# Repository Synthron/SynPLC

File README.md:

# SynPLC

Open Source modular PLC with Microcontrollers

**WORK IN PROGRESS**

# To-Dos

## Repo

- [x] Rewrite documentation in english
- [x] add reviewed PCBs
- [ ] fill out tech specs of modules once programmed
- [ ] Cleanup Repo
  - [ ] better folder structure
  - [X] delete obsolete files

## Hardware

- [x] Order new PCBs with STM32s
- [x] Assemble new PCBs
- [ ] Test new hardware
  - [X] DO
  - [X] DI
  - [ ] AO
  - [ ] AI
  - [ ] XT
- [ ] New Modules
  - [ ] CPU V2
    - [X] Layout
    - [X] Review
    - [ ] Ordered
  - [ ] Relais Module
  - [ ] PWM Module

## Software

- [ ] Write Software for new PCBs
  - [ ] CPU
  - [ ] DO
  - [ ] DI
  - [ ] AO
  - [ ] AI
  - [ ] XT
- [ ] Porting of SR485 protocol to new hardware
  - [ ] Make it use Interrupts
  - [ ] Make it more efficient (processing)
  - [ ] implement failsafes when no answer
- [ ] Define and program CAN protocol
- [ ] Write generalized Code for CPU
- [ ] ~~define structured Text~~ (postponed)
- [ ] ~~import structured text and parse into running code~~ (postponed)

## Possible Fixes

- [x] ~~MAX485 with 5V supply voltage on all IO modules ?~~
  - changed to 3V3 on the CPU
- [x] DIs and DO (alt. switches) re-soldering (dead channels)
- [x] better connector for CPU
- [ ] parametrize RS485 lib a bit more (tbd)

## issues

- [x] weird additional bytes sent by slave after ACK and CS???
  - resolved

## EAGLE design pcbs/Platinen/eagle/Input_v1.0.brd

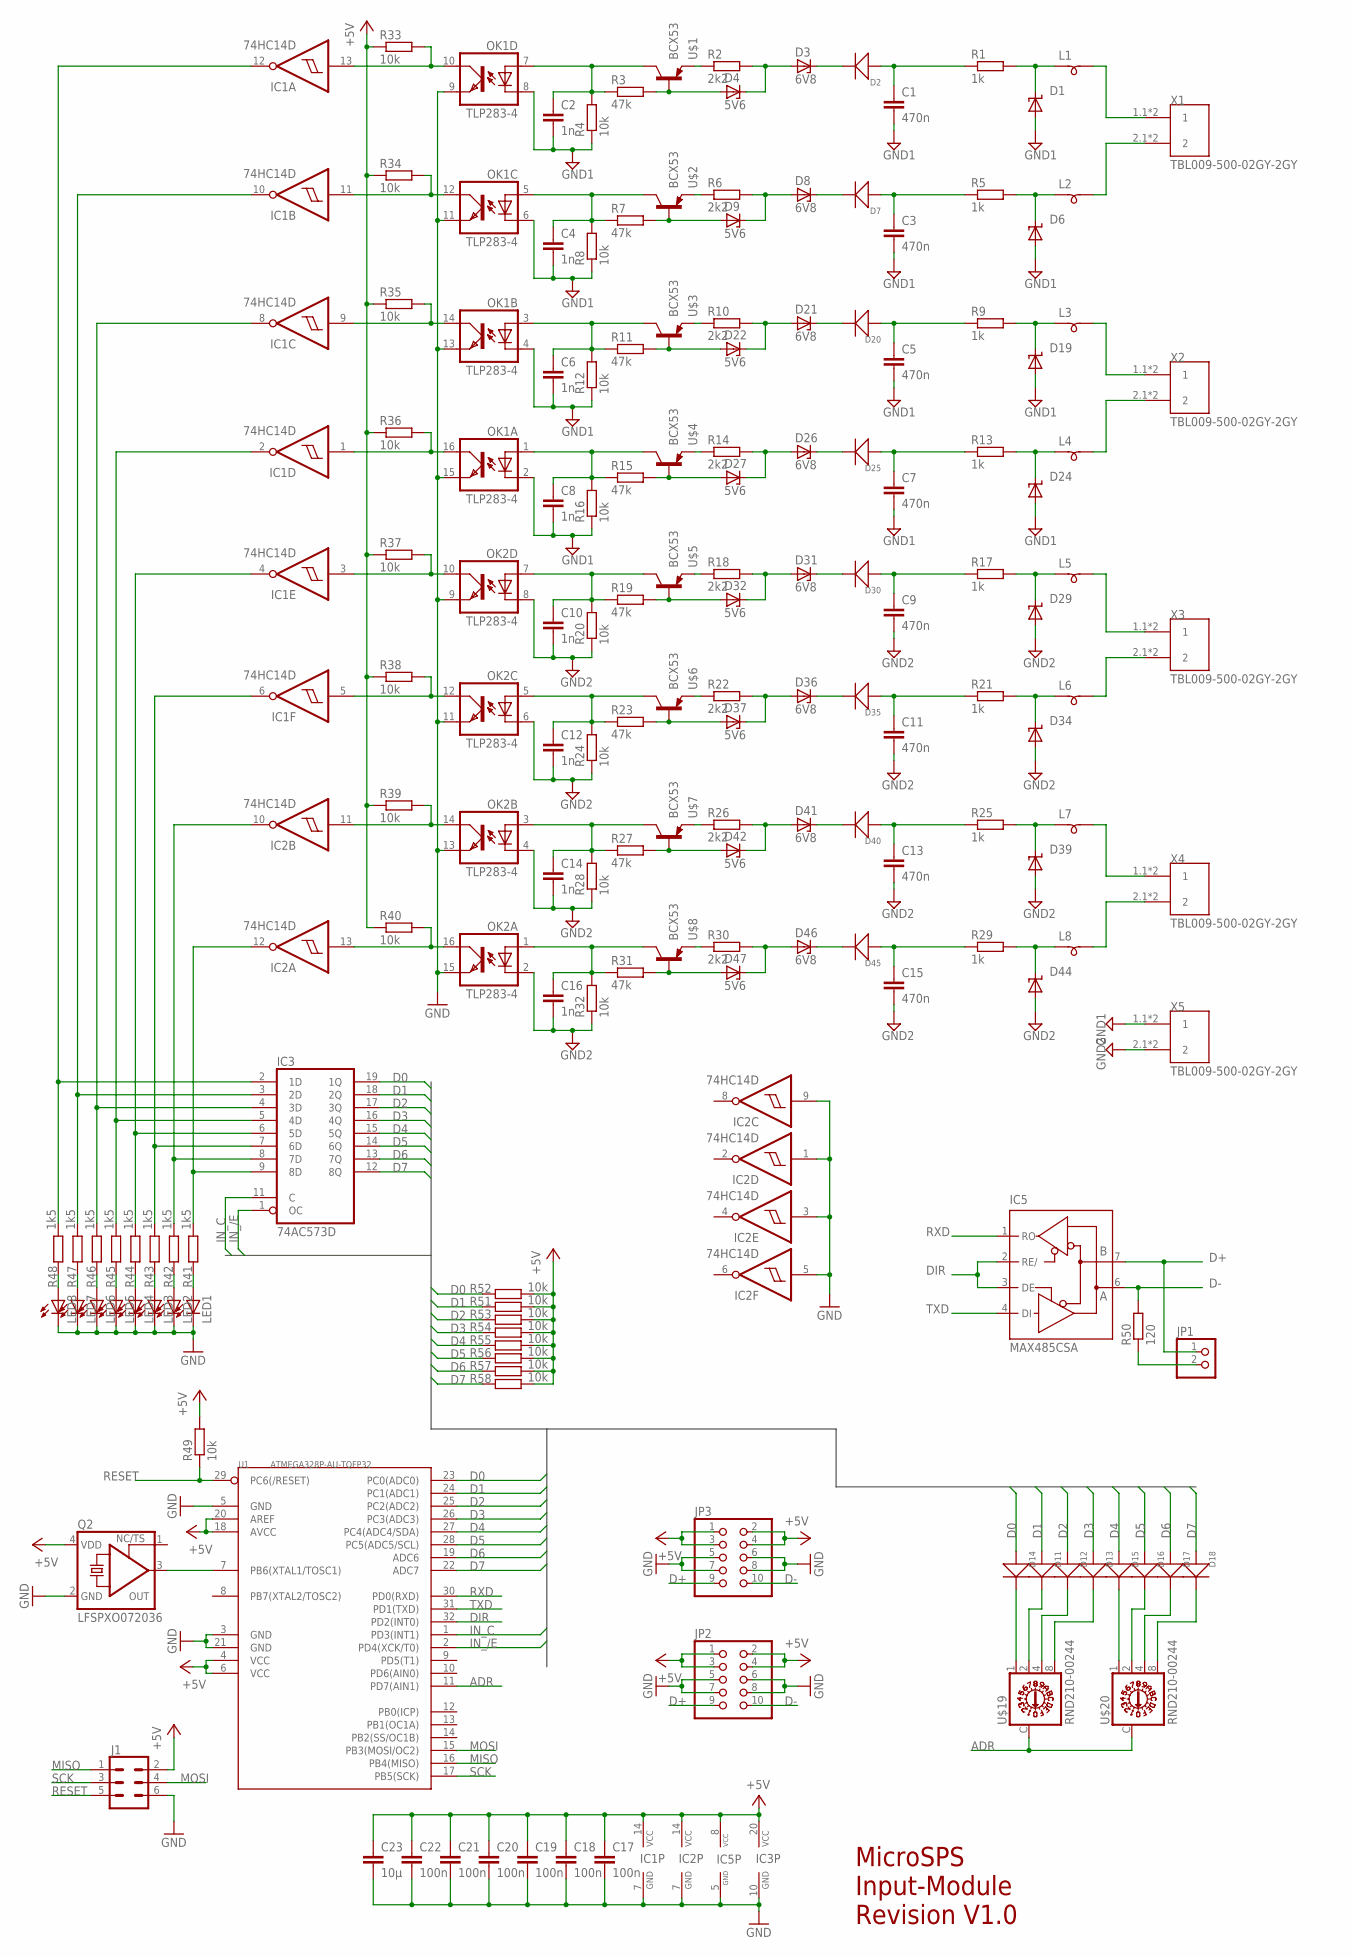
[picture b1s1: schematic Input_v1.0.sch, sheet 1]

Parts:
C1, C3, C5, C7, C9, C11, C13, C15: 470n; C0805
C2, C4, C6, C8, C10, C12, C14, C16: 1n; C0805
C17, C18, C19, C20, C21, C22: 100n; C0805
C23: 10µ; C0805
D1, D6, D19, D24, D29, D34, D39, D44: SUPPRESSOR-SMBJ; SMBJ
D2, D7, D11, D12, D13, D14, D15, D16, D17, D18, D20, D25, D30, D35, D40, D45: DIODE'1N4148-SMD'; LL-34
D3, D8, D21, D26, D31, D36, D41, D46: 6V8; SOD80C
D4, D9, D22, D27, D32, D37, D42, D47: 5V6; SOD80C
IC1, IC2: 74HC14D; SO14
IC3: 74AC573D; SO20W
IC5: MAX485CSA; SO08
J1: CONN_03X2FEMALE_SMD; 2X3_SMD
JP1: PINHD-1X2; 1X02
JP2, JP3: PINHD-2X5/90; 2X05/90
L1, L2, L3, L4, L5, L6, L7, L8: SM-B5
LED1, LED2, LED3, LED4, LED5, LED6, LED7, LED8: LED3MM
OK1, OK2: TLP283-4; MINI-FLAT-16
Q2: LFSPXO072036; 5.0X3.2_KXO-56
R1, R5, R9, R13, R17, R21, R25, R29: 1k; R0805
R2, R6, R10, R14, R18, R22, R26, R30: 2k2; R0805
R3, R7, R11, R15, R19, R23, R27, R31: 47k; R0805
R4, R8, R12, R16, R20, R24, R28, R32, R33, R34, R35, R36, R37, R38, R39, R40, R49, R51, R52, R53, R54, R55, R56, R57, R58: 10k; R0805
R41, R42, R43, R44, R45, R46, R47, R48: 1k5; R0805
R50: 120; R0805
U1: ATMEGA328P-AU-TQFP32; TQFP32-0.8-7X7MM
U$1, U$2, U$3, U$4, U$5, U$6, U$7, U$8: BCX53; SOT89
U$19, U$20: RND210-00244
X1, X2, X3, X4, X5: TBL009-500-02GY-2GY

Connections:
+5V: C17.1, C18.1, C19.1, C20.1, C21.1, C22.1, C23.1, IC1.14 (VCC), IC2.14 (VCC), IC3.20 (VCC), IC5.8 (VCC), J1.2, JP2.1, JP2.2, JP2.3, JP2.4, JP3.1, JP3.2, JP3.3, JP3.4, Q2.4 (VDD), R33.1, R34.1, R35.1, R36.1, R37.1, R38.1, R39.1, R40.1, R49.2, R51.2, R52.2, R53.2, R54.2, R55.2, R56.2, R57.2, R58.2, U1.4 (VCC), U1.6 (VCC), U1.18 (AVCC), U1.20 (AREF)
ADR: U1.11 (PD7(AIN1)), U$19.C, U$20.C
D0: D14.A (+), IC3.19 (1Q), R52.1, U1.23 (PC0(ADC0))
D1: D11.A (+), IC3.18 (2Q), R51.1, U1.24 (PC1(ADC1))
D2: D12.A (+), IC3.17 (3Q), R53.1, U1.25 (PC2(ADC2))
D3: D13.A (+), IC3.16 (4Q), R54.1, U1.26 (PC3(ADC3))
D4: D15.A (+), IC3.15 (5Q), R55.1, U1.27 (PC4(ADC4/SDA))
D5: D16.A (+), IC3.14 (6Q), R56.1, U1.28 (PC5(ADC5/SCL))
D6: D17.A (+), IC3.13 (7Q), R57.1, U1.19 (ADC6)
D7: D18.A (+), IC3.12 (8Q), R58.1, U1.22 (ADC7)
D+: IC5.7 (B), JP1.1, JP2.9, JP3.9
D-: IC5.6 (A), JP2.10, JP3.10, R50.2
DIR: IC5.2 (RE/), IC5.3 (DE), U1.32 (PD2(INT0))
GND: C17.2, C18.2, C19.2, C20.2, C21.2, C22.2, C23.2, IC1.7 (GND), IC2.1 (I), IC2.3 (I), IC2.5 (I), IC2.7 (GND), IC2.9 (I), IC3.10 (GND), IC5.5 (GND), J1.6, JP2.5, JP2.6, JP2.7, JP2.8, JP3.5, JP3.6, JP3.7, JP3.8, LED1.K (C), LED2.K (C), LED3.K (C), LED4.K (C), LED5.K (C), LED6.K (C), LED7.K (C), LED8.K (C), OK1.9 (EMIT), OK1.11 (EMIT), OK1.13 (EMIT), OK1.15 (EMIT), OK2.9 (EMIT), OK2.11 (EMIT), OK2.13 (EMIT), OK2.15 (EMIT), Q2.2 (GND), U1.3 (GND), U1.5 (GND), U1.21 (GND)
GND1: C1.2, C2.2, C3.2, C4.2, C5.2, C6.2, C7.2, C8.2, D1.A, D6.A, D19.A, D24.A, OK1.2 (C), OK1.4 (C), OK1.6 (C), OK1.8 (C), R4.1, R8.1, R12.1, R16.1, X5.1.1 (1), X5.1.2 (1)
GND2: C9.2, C10.2, C11.2, C12.2, C13.2, C14.2, C15.2, C16.2, D29.A, D34.A, D39.A, D44.A, OK2.2 (C), OK2.4 (C), OK2.6 (C), OK2.8 (C), R20.1, R24.1, R28.1, R32.1, X5.2.1 (2), X5.2.2 (2)
IN_/E: IC3.1 (OC), U1.2 (PD4(XCK/T0))
IN_C: IC3.11 (C), U1.1 (PD3(INT1))
MISO: J1.1, U1.16 (PB4(MISO))
MOSI: J1.4, U1.15 (PB3(MOSI/OC2))
unnamed: D3.A, D4.C, R2.2
unnamed: D2.C (-), D3.C
unnamed: C1.1, D2.A (+), R1.1
unnamed: D1.C, L1.1, R1.2
unnamed: D4.A, R3.2, U$1.1 (B)
unnamed: R2.1, U$1.3 (E)
unnamed: C2.1, OK1.7 (A), R3.1, R4.2, U$1.2 (C), U$1.2.1 (C)
unnamed: IC1.13 (I), OK1.10 (COL), R33.2
unnamed: L1.2, X1.1.1 (1), X1.1.2 (1)
unnamed: D8.A, D9.C, R6.2
unnamed: D7.C (-), D8.C
unnamed: C3.1, D7.A (+), R5.1
unnamed: D6.C, L2.1, R5.2
unnamed: R6.1, U$2.3 (E)
unnamed: L2.2, X1.2.1 (2), X1.2.2 (2)
unnamed: D9.A, R7.2, U$2.1 (B)
unnamed: C4.1, OK1.5 (A), R7.1, R8.2, U$2.2 (C), U$2.2.1 (C)
unnamed: IC1.11 (I), OK1.12 (COL), R34.2
unnamed: D21.A, D22.C, R10.2
unnamed: D20.C (-), D21.C
unnamed: C5.1, D20.A (+), R9.1
unnamed: D19.C, L3.1, R9.2
unnamed: R10.1, U$3.3 (E)
unnamed: L3.2, X2.1.1 (1), X2.1.2 (1)
unnamed: D22.A, R11.2, U$3.1 (B)
unnamed: C6.1, OK1.3 (A), R11.1, R12.2, U$3.2 (C), U$3.2.1 (C)
unnamed: IC1.9 (I), OK1.14 (COL), R35.2
unnamed: D26.A, D27.C, R14.2
unnamed: D25.C (-), D26.C
unnamed: C7.1, D25.A (+), R13.1
unnamed: D24.C, L4.1, R13.2
unnamed: R14.1, U$4.3 (E)
unnamed: L4.2, X2.2.1 (2), X2.2.2 (2)
unnamed: D27.A, R15.2, U$4.1 (B)
unnamed: C8.1, OK1.1 (A), R15.1, R16.2, U$4.2 (C), U$4.2.1 (C)
unnamed: IC1.1 (I), OK1.16 (COL), R36.2
unnamed: D31.A, D32.C, R18.2
unnamed: D30.C (-), D31.C
unnamed: C9.1, D30.A (+), R17.1
unnamed: D29.C, L5.1, R17.2
unnamed: R18.1, U$5.3 (E)
unnamed: L5.2, X3.1.1 (1), X3.1.2 (1)
unnamed: D32.A, R19.2, U$5.1 (B)
unnamed: C10.1, OK2.7 (A), R19.1, R20.2, U$5.2 (C), U$5.2.1 (C)
unnamed: IC1.3 (I), OK2.10 (COL), R37.2
unnamed: D36.A, D37.C, R22.2
unnamed: D35.C (-), D36.C
unnamed: C11.1, D35.A (+), R21.1
unnamed: D34.C, L6.1, R21.2
unnamed: R22.1, U$6.3 (E)
unnamed: L6.2, X3.2.1 (2), X3.2.2 (2)
unnamed: D37.A, R23.2, U$6.1 (B)
unnamed: C12.1, OK2.5 (A), R23.1, R24.2, U$6.2 (C), U$6.2.1 (C)
unnamed: IC1.5 (I), OK2.12 (COL), R38.2
unnamed: D41.A, D42.C, R26.2
unnamed: D40.C (-), D41.C
unnamed: C13.1, D40.A (+), R25.1
unnamed: D39.C, L7.1, R25.2
unnamed: R26.1, U$7.3 (E)
unnamed: L7.2, X4.1.1 (1), X4.1.2 (1)
unnamed: D42.A, R27.2, U$7.1 (B)
unnamed: C14.1, OK2.3 (A), R27.1, R28.2, U$7.2 (C), U$7.2.1 (C)
unnamed: IC2.11 (I), OK2.14 (COL), R39.2
unnamed: D46.A, D47.C, R30.2
unnamed: D45.C (-), D46.C
unnamed: C15.1, D45.A (+), R29.1
unnamed: D44.C, L8.1, R29.2
unnamed: R30.1, U$8.3 (E)
unnamed: L8.2, X4.2.1 (2), X4.2.2 (2)
unnamed: D47.A, R31.2, U$8.1 (B)
unnamed: C16.1, OK2.1 (A), R31.1, R32.2, U$8.2 (C), U$8.2.1 (C)
unnamed: IC2.13 (I), OK2.16 (COL), R40.2
unnamed: IC1.12 (O), IC3.2 (1D), R48.2
unnamed: IC1.10 (O), IC3.3 (2D), R47.2
unnamed: IC1.8 (O), IC3.4 (3D), R46.2
unnamed: IC1.2 (O), IC3.5 (4D), R45.2
unnamed: IC1.4 (O), IC3.6 (5D), R44.2
unnamed: IC1.6 (O), IC3.7 (6D), R43.2
unnamed: IC2.10 (O), IC3.8 (7D), R42.2
unnamed: IC2.12 (O), IC3.9 (8D), R41.2
unnamed: LED8.A, R48.1
unnamed: LED7.A, R47.1
unnamed: LED6.A, R46.1
unnamed: LED5.A, R45.1
unnamed: LED4.A, R44.1
unnamed: LED3.A, R43.1
unnamed: LED2.A, R42.1
unnamed: LED1.A, R41.1
unnamed: Q2.3 (OUT), U1.7 (PB6(XTAL1/TOSC1))
unnamed: JP1.2, R50.1
unnamed: D14.C (-), U$19.1
unnamed: D11.C (-), U$19.2
unnamed: D12.C (-), U$19.4
unnamed: D13.C (-), U$19.8
unnamed: D15.C (-), U$20.1
unnamed: D16.C (-), U$20.2
unnamed: D17.C (-), U$20.4
unnamed: D18.C (-), U$20.8
RESET: J1.5, R49.1, U1.29 (PC6(/RESET))
RXD: IC5.1 (RO), U1.30 (PD0(RXD))
SCK: J1.3, U1.17 (PB5(SCK))
TXD: IC5.4 (DI), U1.31 (PD1(TXD))

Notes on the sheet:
MicroSPS Input-Module Revision V1.0

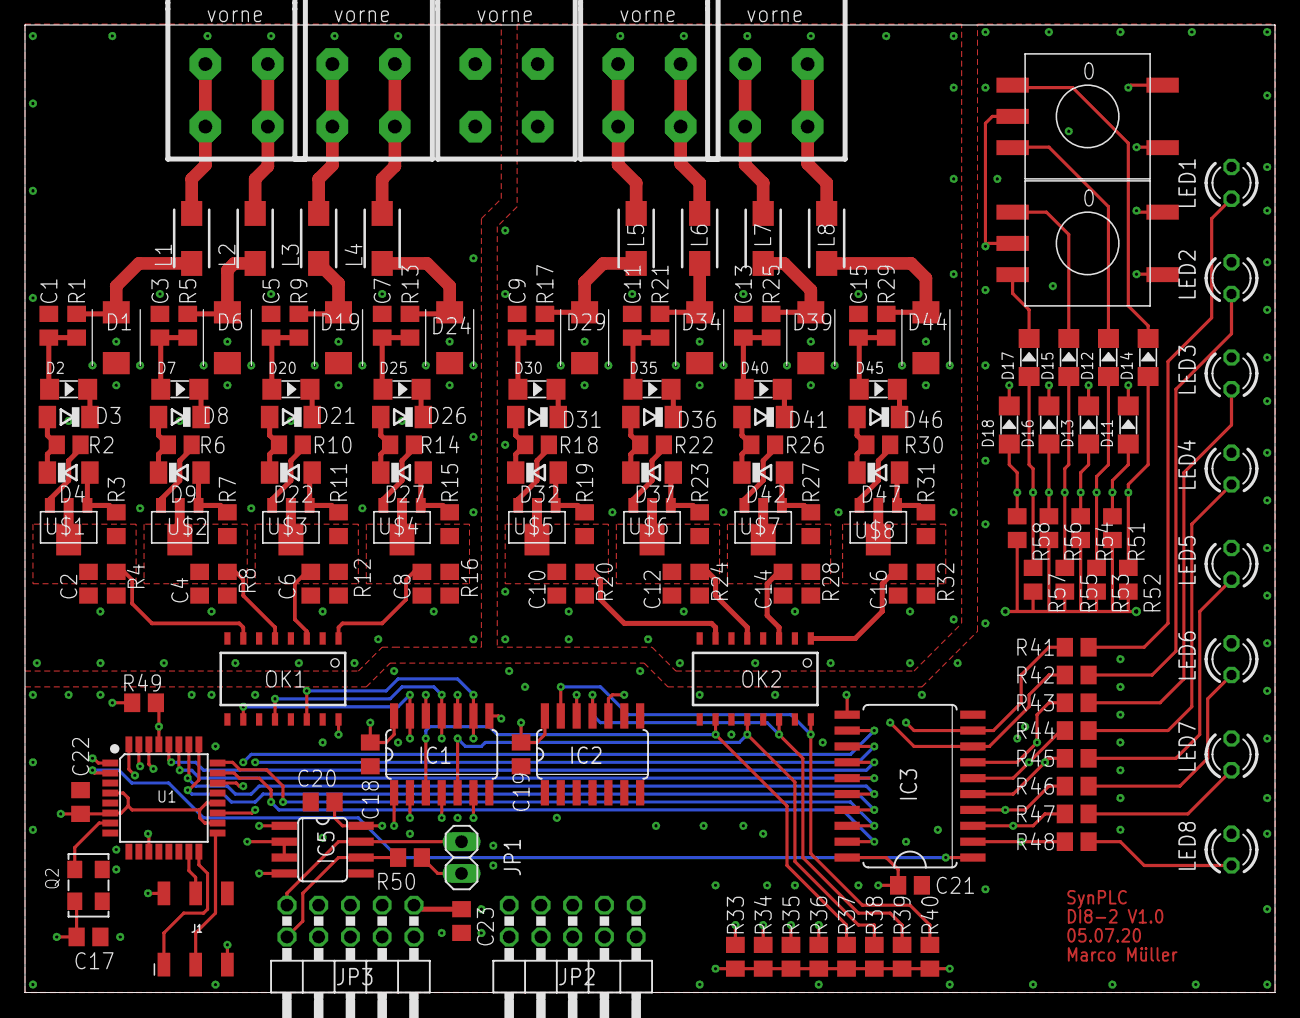
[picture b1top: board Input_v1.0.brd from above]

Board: 4 copper layers, 100.0 x 77.4 mm, 164 parts (0 on the bottom side), 122 nets.

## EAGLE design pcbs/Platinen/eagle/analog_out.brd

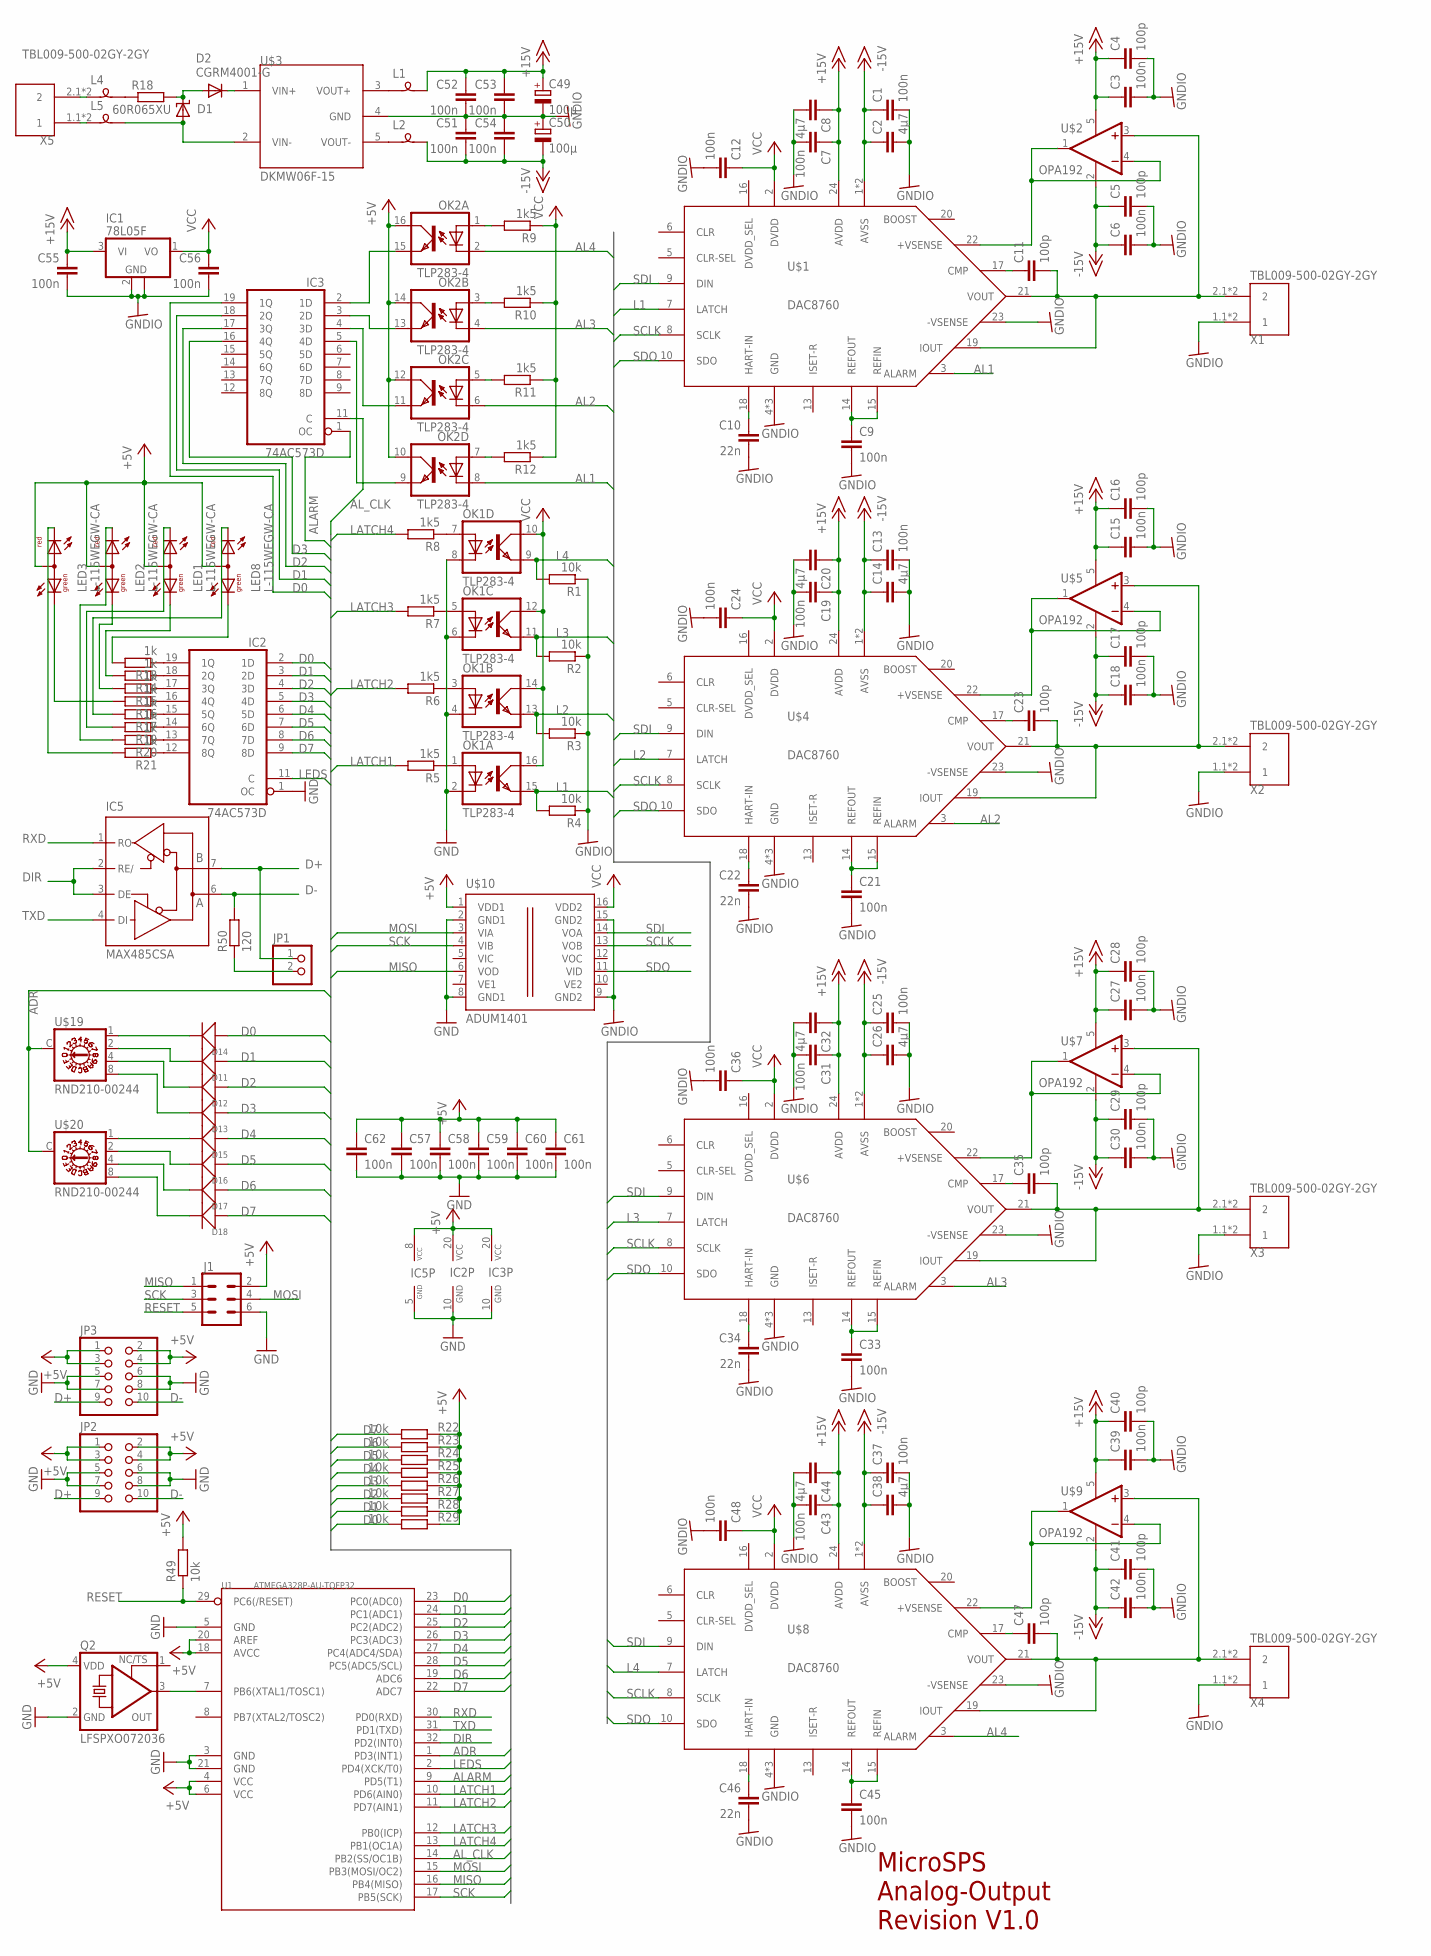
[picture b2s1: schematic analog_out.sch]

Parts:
C1, C3, C6, C7, C9, C12, C13, C15, C18, C19, C21, C24, C25, C27, C30, C31, C33, C36, C37, C39, C42, C43, C45, C48, C51, C52, C53, C54, C55, C56, C57, C58, C59, C60, C61, C62: 100n; C0805
C2, C8, C14, C20, C26, C32, C38, C44: 4µ7; C0805
C4, C5, C11, C16, C17, C23, C28, C29, C35, C40, C41, C47: 100p; C0805
C10, C22, C34, C46: 22n; C0805
C49, C50: 100µ; 153CLV-0505
D1: SUPPRESSOR-SMBJ; SMBJ
D2: CGRM4001-G; SOD-123_MINI-SMA
D11, D12, D13, D14, D15, D16, D17, D18: DIODE'1N4148-SMD'; LL-34
IC1: 78L05F; SOT89
IC2, IC3: 74AC573D; SO20W
IC5: MAX485CSA; SO08
J1: CONN_03X2FEMALE_SMD; 2X3_SMD
JP1: PINHD-1X2; 1X02
JP2, JP3: PINHD-2X5/90; 2X05/90
L1, L2, L4, L5: SM-B5
LED1, LED2, LED3, LED8: L-115WEGW-CA; DUOLED-A-3MM
OK1, OK2: TLP283-4; MINI-FLAT-16
Q2: LFSPXO072036; 5.0X3.2_KXO-56
R1, R2, R3, R4, R22, R23, R24, R25, R26, R27, R28, R29, R49: 10k; R0805
R5, R6, R7, R8, R9, R10, R11, R12: 1k5; R0805
R13, R14, R15, R16, R17, R19, R20, R21: 1k; R0805
R18: 60R065XU; 0204/5
R50: 120; R0805
U1: ATMEGA328P-AU-TQFP32; TQFP32-0.8-7X7MM
U$1, U$4, U$6, U$8: DAC8760; HTSSOP24PWP
U$2, U$5, U$7, U$9: OPA192; SOT23-DBV
U$3: DKMW06F-15; DKWM06
U$10: ADUM1401; SO-16W
U$19, U$20: RND210-00244
X1, X2, X3, X4, X5: TBL009-500-02GY-2GY

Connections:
+5V: C57.1, C58.1, C59.1, C60.1, C61.1, C62.1, IC2.20 (VCC), IC3.20 (VCC), IC5.8 (VCC), J1.2, JP2.1, JP2.2, JP2.3, JP2.4, JP3.1, JP3.2, JP3.3, JP3.4, LED1.2 (A), LED2.2 (A), LED3.2 (A), LED8.2 (A), OK2.10 (COL), OK2.12 (COL), OK2.14 (COL), OK2.16 (COL), Q2.4 (VDD), R22.1, R23.1, R24.1, R25.1, R26.1, R27.1, R28.1, R29.1, R49.2, U1.4 (VCC), U1.6 (VCC), U1.18 (AVCC), U1.20 (AREF), U$10.1 (VDD1)
+15V: C3.1, C4.1, C7.1, C8.1, C15.1, C16.1, C19.1, C20.1, C27.1, C28.1, C31.1, C32.1, C39.1, C40.1, C43.1, C44.1, C49.+, C52.1, C53.1, C55.1, IC1.3 (VI), L1.1, U$1.24 (AVDD), U$2.5 (V+), U$4.24 (AVDD), U$5.5 (V+), U$6.24 (AVDD), U$7.5 (V+), U$8.24 (AVDD), U$9.5 (V+)
-15V: C1.1, C2.1, C5.1, C6.1, C13.1, C14.1, C17.1, C18.1, C25.1, C26.1, C29.1, C30.1, C37.1, C38.1, C41.1, C42.1, C50.-, C51.2, C54.2, L2.1, U$1.1 (AVSS), U$1.EXP (AVSS), U$2.2 (V-), U$4.1 (AVSS), U$4.EXP (AVSS), U$5.2 (V-), U$6.1 (AVSS), U$6.EXP (AVSS), U$7.2 (V-), U$8.1 (AVSS), U$8.EXP (AVSS), U$9.2 (V-)
ADR: U1.1 (PD3(INT1)), U$19.C, U$20.C
AL1: OK2.8 (C), U$1.3 (ALARM)
AL2: OK2.6 (C), U$4.3 (ALARM)
AL3: OK2.4 (C), U$6.3 (ALARM)
AL4: OK2.2 (C), U$8.3 (ALARM)
ALARM: IC3.1 (OC), U1.9 (PD5(T1))
AL_CLK: IC3.11 (C), U1.14 (PB2(SS/OC1B))
D0: D14.A (+), IC2.2 (1D), IC3.19 (1Q), R29.2, U1.23 (PC0(ADC0))
D1: D11.A (+), IC2.3 (2D), IC3.18 (2Q), R28.2, U1.24 (PC1(ADC1))
D2: D12.A (+), IC2.4 (3D), IC3.17 (3Q), R27.2, U1.25 (PC2(ADC2))
D3: D13.A (+), IC2.5 (4D), IC3.16 (4Q), R26.2, U1.26 (PC3(ADC3))
D4: D15.A (+), IC2.6 (5D), R25.2, U1.27 (PC4(ADC4/SDA))
D5: D16.A (+), IC2.7 (6D), R24.2, U1.28 (PC5(ADC5/SCL))
D6: D17.A (+), IC2.8 (7D), R23.2, U1.19 (ADC6)
D7: D18.A (+), IC2.9 (8D), R22.2, U1.22 (ADC7)
D+: IC5.7 (B), JP1.1, JP2.9, JP3.9
D-: IC5.6 (A), JP2.10, JP3.10, R50.2
DIR: IC5.2 (RE/), IC5.3 (DE), U1.32 (PD2(INT0))
GND: C57.2, C58.2, C59.2, C60.2, C61.2, C62.2, IC2.1 (OC), IC2.10 (GND), IC3.10 (GND), IC5.5 (GND), J1.6, JP2.5, JP2.6, JP2.7, JP2.8, JP3.5, JP3.6, JP3.7, JP3.8, OK1.2 (C), OK1.4 (C), OK1.6 (C), OK1.8 (C), Q2.2 (GND), U1.3 (GND), U1.5 (GND), U1.21 (GND), U$10.2 (GND1), U$10.8 (GND1)
GNDIO: C1.2, C2.2, C3.2, C4.2, C5.2, C6.2, C7.2, C8.2, C9.2, C10.2, C12.2, C13.2, C14.2, C15.2, C16.2, C17.2, C18.2, C19.2, C20.2, C21.2, C22.2, C24.2, C25.2, C26.2, C27.2, C28.2, C29.2, C30.2, C31.2, C32.2, C33.2, C34.2, C36.2, C37.2, C38.2, C39.2, C40.2, C41.2, C42.2, C43.2, C44.2, C45.2, C46.2, C48.2, C49.-, C50.+, C51.1, C52.2, C53.2, C54.1, C55.2, C56.2, IC1.2 (GND), IC1.2@1 (GND), R1.1, R2.1, R3.1, R4.1, U$1.4 (GND), U$1.11 (GND), U$1.12 (GND), U$1.23 (-VSENSE), U$3.4 (GND), U$4.4 (GND), U$4.11 (GND), U$4.12 (GND), U$4.23 (-VSENSE), U$6.4 (GND), U$6.11 (GND), U$6.12 (GND), U$6.23 (-VSENSE), U$8.4 (GND), U$8.11 (GND), U$8.12 (GND), U$8.23 (-VSENSE), U$10.9 (GND2), U$10.15 (GND2), X1.1.1 (1), X1.1.2 (1), X2.1.1 (1)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
L1: OK1.15 (EMIT), R4.2, U$1.7 (LATCH)
L2: OK1.13 (EMIT), R3.2, U$4.7 (LATCH)
L3: OK1.11 (EMIT), R2.2, U$6.7 (LATCH)
L4: OK1.9 (EMIT), R1.2, U$8.7 (LATCH)
LATCH1: R5.2, U1.10 (PD6(AIN0))
LATCH2: R6.2, U1.11 (PD7(AIN1))
LATCH3: R7.2, U1.12 (PB0(ICP))
LATCH4: R8.2, U1.13 (PB1(OC1A))
LEDS: IC2.11 (C), U1.2 (PD4(XCK/T0))
MISO: J1.1, U1.16 (PB4(MISO)), U$10.6 (VOD)
MOSI: J1.4, U1.15 (PB3(MOSI/OC2)), U$10.3 (VIA)
unnamed: C9.1, U$1.14 (REFOUT), U$1.15 (REFIN)
unnamed: C10.1, U$1.18 (HART-IN)
unnamed: C11.1, U$1.17 (CMP)
unnamed: C23.2, U$4.19 (IOUT), U$4.21 (VOUT), U$5.3 (+IN), X2.2.1 (2), X2.2.2 (2)
unnamed: C11.2, U$1.19 (IOUT), U$1.21 (VOUT), U$2.3 (+IN), X1.2.1 (2), X1.2.2 (2)
unnamed: U$1.22 (+VSENSE), U$2.1 (OUT), U$2.4 (-IN)
unnamed: U$4.22 (+VSENSE), U$5.1 (OUT), U$5.4 (-IN)
unnamed: C21.1, U$4.14 (REFOUT), U$4.15 (REFIN)
unnamed: C22.1, U$4.18 (HART-IN)
unnamed: C23.1, U$4.17 (CMP)
unnamed: C35.2, U$6.19 (IOUT), U$6.21 (VOUT), U$7.3 (+IN), X3.2.1 (2), X3.2.2 (2)
unnamed: U$6.22 (+VSENSE), U$7.1 (OUT), U$7.4 (-IN)
unnamed: C33.1, U$6.14 (REFOUT), U$6.15 (REFIN)
unnamed: C34.1, U$6.18 (HART-IN)
unnamed: C35.1, U$6.17 (CMP)
unnamed: C47.2, U$8.19 (IOUT), U$8.21 (VOUT), U$9.3 (+IN), X4.2.1 (2), X4.2.2 (2)
unnamed: U$8.22 (+VSENSE), U$9.1 (OUT), U$9.4 (-IN)
unnamed: C45.1, U$8.14 (REFOUT), U$8.15 (REFIN)
unnamed: C46.1, U$8.18 (HART-IN)
unnamed: C47.1, U$8.17 (CMP)
unnamed: L4.2, X5.2.1 (2), X5.2.2 (2)
unnamed: L5.2, X5.1.1 (1), X5.1.2 (1)
unnamed: L4.1, R18.1
unnamed: D1.C, D2.A, R18.2
unnamed: D1.A, L5.1, U$3.2 (VIN-)
unnamed: D2.C, U$3.1 (VIN+)
unnamed: L1.2, U$3.3 (VOUT+)
unnamed: L2.2, U$3.5 (VOUT-)
unnamed: IC2.19 (1Q), R13.1
unnamed: IC2.18 (2Q), R14.1
unnamed: IC2.17 (3Q), R15.1
unnamed: IC2.16 (4Q), R16.1
unnamed: OK2.1 (A), R9.2
unnamed: OK1.1 (A), R5.1
unnamed: OK1.3 (A), R6.1
unnamed: OK1.5 (A), R7.1
unnamed: OK1.7 (A), R8.1
unnamed: OK2.3 (A), R10.2
unnamed: OK2.5 (A), R11.2
unnamed: OK2.7 (A), R12.2
unnamed: IC2.15 (5Q), R17.1
unnamed: IC2.14 (6Q), R19.1
unnamed: IC2.13 (7Q), R20.1
unnamed: IC2.12 (8Q), R21.1
unnamed: LED8.1 (CG), R13.2
unnamed: LED1.1 (CG), R14.2
unnamed: LED2.1 (CG), R15.2
unnamed: LED3.1 (CG), R16.2
unnamed: LED8.3 (CR), R17.2
unnamed: LED1.3 (CR), R19.2
unnamed: LED2.3 (CR), R20.2
unnamed: LED3.3 (CR), R21.2
unnamed: IC3.5 (4D), OK2.9 (EMIT)
unnamed: IC3.4 (3D), OK2.11 (EMIT)
unnamed: IC3.3 (2D), OK2.13 (EMIT)
unnamed: IC3.2 (1D), OK2.15 (EMIT)
unnamed: Q2.3 (OUT), U1.7 (PB6(XTAL1/TOSC1))
unnamed: JP1.2, R50.1
unnamed: D14.C (-), U$19.1
unnamed: D11.C (-), U$19.2
unnamed: D12.C (-), U$19.4
unnamed: D13.C (-), U$19.8
unnamed: D15.C (-), U$20.1
unnamed: D16.C (-), U$20.2
unnamed: D17.C (-), U$20.4
unnamed: D18.C (-), U$20.8
RESET: J1.5, R49.1, U1.29 (PC6(/RESET))
RXD: IC5.1 (RO), U1.30 (PD0(RXD))
SCK: J1.3, U1.17 (PB5(SCK)), U$10.4 (VIB)
SCLK: U$1.8 (SCLK), U$4.8 (SCLK), U$6.8 (SCLK), U$8.8 (SCLK), U$10.13 (VOB)
SDI: U$1.9 (DIN), U$4.9 (DIN), U$6.9 (DIN), U$8.9 (DIN), U$10.14 (VOA)
SDO: U$1.10 (SDO), U$4.10 (SDO), U$6.10 (SDO), U$8.10 (SDO), U$10.11 (VID)
TXD: IC5.4 (DI), U1.31 (PD1(TXD))
VCC: C12.1, C24.1, C36.1, C48.1, C56.1, IC1.1 (VO), OK1.10 (COL), OK1.12 (COL), OK1.14 (COL), OK1.16 (COL), R9.1, R10.1, R11.1, R12.1, U$1.2 (DVDD), U$4.2 (DVDD), U$6.2 (DVDD), U$8.2 (DVDD), U$10.16 (VDD2)

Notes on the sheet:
MicroSPS Analog-Output Revision V1.0

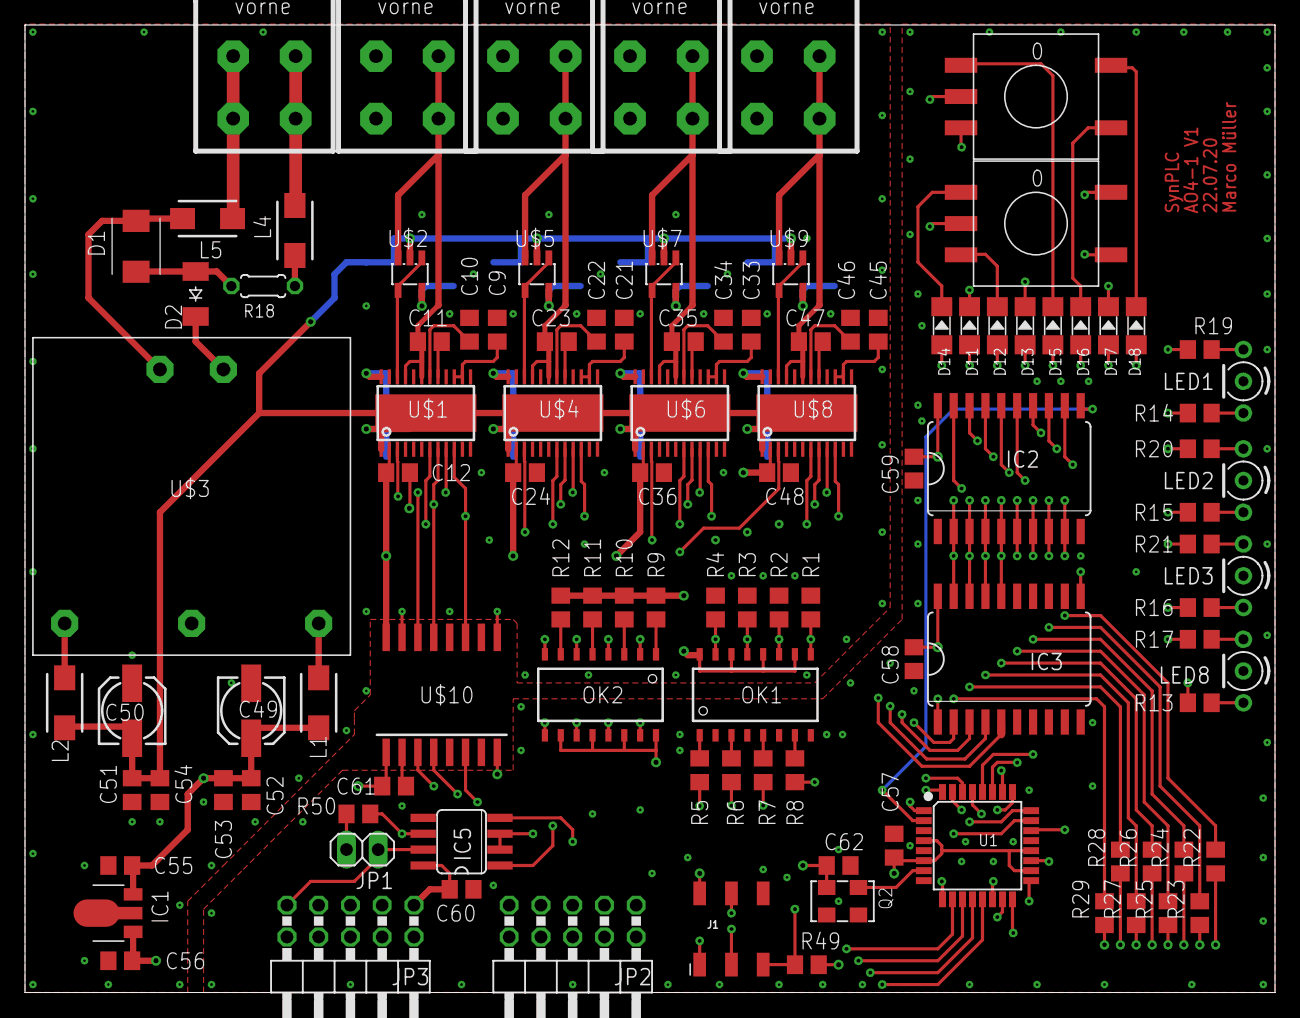
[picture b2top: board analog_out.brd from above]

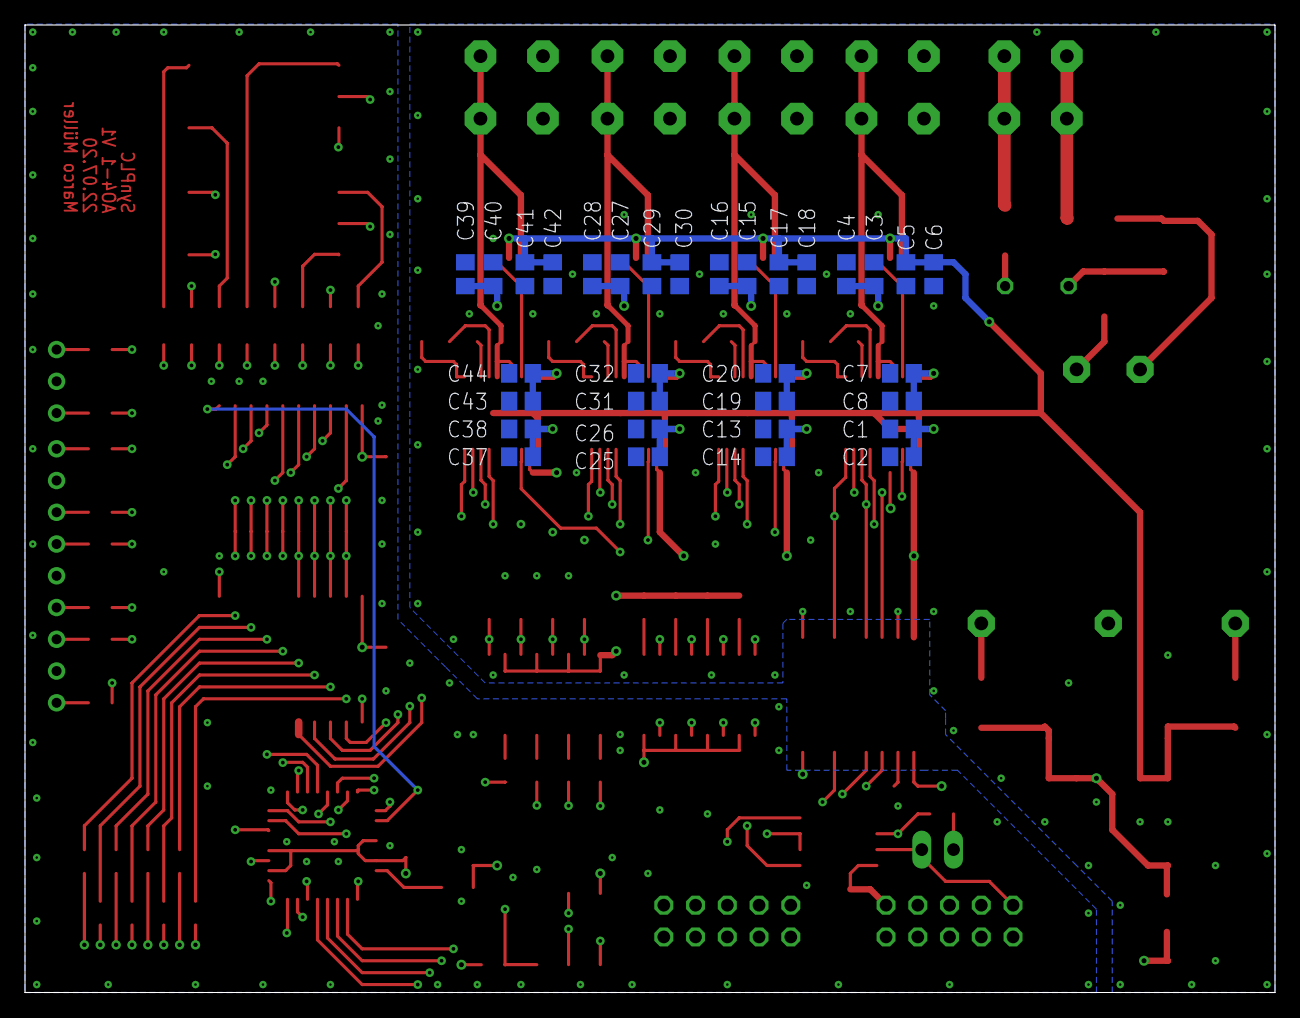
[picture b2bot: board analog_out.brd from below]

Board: 4 copper layers, 100.0 x 77.4 mm, 140 parts (32 on the bottom side), 108 nets.

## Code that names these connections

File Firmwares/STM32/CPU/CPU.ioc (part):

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Mcu.Name=STM32F103C(8-B)Tx
Mcu.Package=LQFP48
Mcu.UserName=STM32F103C8Tx
PA10.GPIOParameters=GPIO_Label
PA10.GPIO_Label=ERROR
PA10.Signal=GPIO_Output
PA11.Mode=Device
PA11.Signal=USB_DM
PA12.Mode=Device
PA12.Signal=USB_DP
PA13.Mode=Serial_Wire
PA13.Signal=SYS_JTMS-SWDIO
PA14.Mode=Serial_Wire
PA14.Signal=SYS_JTCK-SWCLK
PA15.GPIOParameters=GPIO_Label
PA15.GPIO_Label=RUN
PA15.Signal=GPIO_Output
PA2.Mode=Asynchronous
PA2.Signal=USART2_TX
PA3.Mode=Asynchronous
PA3.Signal=USART2_RX
PA9.GPIOParameters=GPIO_Label
PA9.GPIO_Label=BOOT
PA9.Signal=GPIO_Output
PB10.Mode=Asynchronous
PB10.Signal=USART3_TX
PB11.Mode=Asynchronous
PB11.Signal=USART3_RX
PB12.GPIOParameters=GPIO_Label
PB12.GPIO_Label=CS1
PB12.Signal=GPIO_Output
PB13.Mode=Full_Duplex_Master
PB13.Signal=SPI2_SCK
PB14.Mode=Full_Duplex_Master
PB14.Signal=SPI2_MISO
PB15.Mode=Full_Duplex_Master
PB15.Signal=SPI2_MOSI
PB3.GPIOParameters=GPIO_Label
PB3.GPIO_Label=HEARTBEAT
PB3.Signal=GPIO_Output
PB4.GPIOParameters=GPIO_Label
PB4.GPIO_Label=FLASH
PB4.Signal=GPIO_Output
PB5.GPIOParameters=GPIO_Label
PB5.GPIO_Label=DIR
PB5.Signal=GPIO_Output
PB8.Mode=CAN_Activate
PB8.Signal=CAN_RX
PB9.Mode=CAN_Activate
PB9.Signal=CAN_TX
PC14-OSC32_IN.Mode=LSE-External-Oscillator
PC14-OSC32_IN.Signal=RCC_OSC32_IN
PC15-OSC32_OUT.Mode=LSE-External-Oscillator
PC15-OSC32_OUT.Signal=RCC_OSC32_OUT
PD0-OSC_IN.Mode=HSE-External-Oscillator
PD0-OSC_IN.Signal=RCC_OSC_IN
PD1-OSC_OUT.Mode=HSE-External-Oscillator
PD1-OSC_OUT.Signal=RCC_OSC_OUT
RCC.SYSCLKFreq_VALUE=48000000
RCC.SYSCLKSource=RCC_SYSCLKSOURCE_PLLCLK
board=custom

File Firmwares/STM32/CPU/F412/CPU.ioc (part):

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Mcu.Name=STM32F412R(E-G)Tx
Mcu.Package=LQFP64
Mcu.UserName=STM32F412RETx
PA10.Mode=Asynchronous
PA10.Signal=USART1_RX
PA11.Mode=Device_Only
PA11.Signal=USB_OTG_FS_DM
PA12.Mode=Device_Only
PA12.Signal=USB_OTG_FS_DP
PA13.Mode=Serial_Wire
PA13.Signal=SYS_JTMS-SWDIO
PA14.Mode=Serial_Wire
PA14.Signal=SYS_JTCK-SWCLK
PA2.Mode=Asynchronous
PA2.Signal=USART2_TX
PA3.Mode=Asynchronous
PA3.Signal=USART2_RX
PA4.GPIOParameters=GPIO_Label
PA4.GPIO_Label=SDIO_CardDetect
PA4.Signal=GPIO_Input
PA5.GPIOParameters=GPIO_Label
PA5.GPIO_Label=SDIO_WriteProtect
PA5.Signal=GPIO_Input
PA6.Mode=SD_4_bits_Wide_bus
PA6.Signal=SDIO_CMD
PA8.GPIOParameters=GPIO_Label
PA8.GPIO_Label=RS485_DIR
PA8.Signal=GPIO_Output
PA9.Mode=Asynchronous
PA9.Signal=USART1_TX
PB0.GPIOParameters=GPIO_Label
PB0.GPIO_Label=TestPoint1
PB0.Signal=GPIO_Output
PB10.Mode=Full_Duplex_Master
PB10.Signal=SPI2_SCK
PB13.GPIOParameters=GPIO_Label
PB13.GPIO_Label=USB_Disconnect
PB13.Signal=GPIO_Output
PB15.Mode=SD_4_bits_Wide_bus
PB15.Signal=SDIO_CK
PB3.GPIOParameters=GPIO_Label
PB3.GPIO_Label=LED_ERROR
PB3.Signal=GPIO_Output
PB4.GPIOParameters=GPIO_Label
PB4.GPIO_Label=LED_RUN
PB4.Signal=GPIO_Output
PB5.GPIOParameters=GPIO_Label
PB5.GPIO_Label=LED_FLASH
PB5.Signal=GPIO_Output
PB6.Mode=I2C
PB6.Signal=I2C1_SCL
PB7.Mode=I2C
PB7.Signal=I2C1_SDA
PB8.Mode=CAN_Activate
PB8.Signal=CAN1_RX
PB9.Mode=CAN_Activate
PB9.Signal=CAN1_TX
PC0.GPIOParameters=GPIO_Label
PC0.GPIO_Label=SPI_CS1
PC0.Signal=GPIO_Output
PC10.Mode=SD_4_bits_Wide_bus
PC10.Signal=SDIO_D2
PC11.Mode=SD_4_bits_Wide_bus
PC11.Signal=SDIO_D3
PC12.GPIOParameters=GPIO_Label
PC12.GPIO_Label=LED_BOOT
PC12.Signal=GPIO_Output
PC14-OSC32_IN.Mode=LSE-External-Oscillator
PC14-OSC32_IN.Signal=RCC_OSC32_IN
PC15-OSC32_OUT.Mode=LSE-External-Oscillator
PC15-OSC32_OUT.Signal=RCC_OSC32_OUT
PC2.Mode=Full_Duplex_Master
PC2.Signal=SPI2_MISO
PC3.Mode=Full_Duplex_Master
PC3.Signal=SPI2_MOSI
PC8.Mode=SD_4_bits_Wide_bus
PC8.Signal=SDIO_D0
PC9.Mode=SD_4_bits_Wide_bus
PC9.Signal=SDIO_D1
PD2.GPIOParameters=GPIO_Label
PD2.GPIO_Label=LED_HEARTBEAT
PD2.Signal=GPIO_Output
PH0\ -\ OSC_IN.Mode=HSE-External-Oscillator
PH0\ -\ OSC_IN.Signal=RCC_OSC_IN
PH1\ -\ OSC_OUT.Mode=HSE-External-Oscillator
PH1\ -\ OSC_OUT.Signal=RCC_OSC_OUT
RCC.HSE_VALUE=12000000
RCC.SYSCLKFreq_VALUE=100000000
RCC.SYSCLKSource=RCC_SYSCLKSOURCE_PLLCLK
board=custom

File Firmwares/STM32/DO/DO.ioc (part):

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Mcu.Name=STM32F103C(8-B)Tx
Mcu.Package=LQFP48
Mcu.UserName=STM32F103C8Tx
PA0-WKUP.GPIOParameters=GPIO_Label
PA0-WKUP.GPIO_Label=ADR0
PA0-WKUP.Signal=GPIO_Input
PA1.GPIOParameters=GPIO_Label
PA1.GPIO_Label=ADR1
PA1.Signal=GPIO_Input
PA10.GPIOParameters=GPIO_Label
PA10.GPIO_Label=CH6
PA10.Signal=GPIO_Output
PA11.GPIOParameters=GPIO_Label
PA11.GPIO_Label=CH7
PA11.Signal=GPIO_Output
PA12.GPIOParameters=GPIO_Label
PA12.GPIO_Label=CH8
PA12.Signal=GPIO_Output
PA13.Mode=Serial_Wire
PA13.Signal=SYS_JTMS-SWDIO
PA14.Mode=Serial_Wire
PA14.Signal=SYS_JTCK-SWCLK
PA2.GPIOParameters=GPIO_Label
PA2.GPIO_Label=ADR2
PA2.Signal=GPIO_Input
PA3.GPIOParameters=GPIO_Label
PA3.GPIO_Label=ADR3
PA3.Signal=GPIO_Input
PA4.GPIOParameters=GPIO_Label
PA4.GPIO_Label=ADR4
PA4.Signal=GPIO_Input
PA5.GPIOParameters=GPIO_Label
PA5.GPIO_Label=CH1
PA5.Signal=GPIO_Output
PA6.GPIOParameters=GPIO_Label
PA6.GPIO_Label=CH2
PA6.Signal=GPIO_Output
PA7.GPIOParameters=GPIO_Label
PA7.GPIO_Label=CH3
PA7.Signal=GPIO_Output
PA8.GPIOParameters=GPIO_Label
PA8.GPIO_Label=CH4
PA8.Signal=GPIO_Output
PA9.GPIOParameters=GPIO_Label
PA9.GPIO_Label=CH5
PA9.Signal=GPIO_Output
PB0.GPIOParameters=GPIO_Label
PB0.GPIO_Label=FB1
PB0.Signal=GPIO_Input
PB1.GPIOParameters=GPIO_Label
PB1.GPIO_Label=FB2
PB1.Signal=GPIO_Input
PB10.Mode=Asynchronous
PB10.Signal=USART3_TX
PB11.Mode=Asynchronous
PB11.Signal=USART3_RX
PB12.GPIOParameters=GPIO_Label
PB12.GPIO_Label=DIR
PB12.Signal=GPIO_Output
PB2.GPIOParameters=GPIO_Label
PB2.GPIO_Label=FB3
PB2.Signal=GPIO_Input
PB3.GPIOParameters=GPIO_Label
PB3.GPIO_Label=FB4
PB3.Signal=GPIO_Input
PB4.GPIOParameters=GPIO_Label
PB4.GPIO_Label=FB5
PB4.Signal=GPIO_Input
PB5.GPIOParameters=GPIO_Label
PB5.GPIO_Label=FB6
PB5.Signal=GPIO_Input
PB6.GPIOParameters=GPIO_Label
PB6.GPIO_Label=FB7
PB6.Signal=GPIO_Input
PB7.GPIOParameters=GPIO_Label
PB7.GPIO_Label=FB8
PB7.Signal=GPIO_Input
PB8.Mode=CAN_Activate
PB8.Signal=CAN_RX
PB9.Mode=CAN_Activate
PB9.Signal=CAN_TX
PD0-OSC_IN.Mode=HSE-External-Oscillator
PD0-OSC_IN.Signal=RCC_OSC_IN
PD1-OSC_OUT.Mode=HSE-External-Oscillator
PD1-OSC_OUT.Signal=RCC_OSC_OUT
RCC.SYSCLKFreq_VALUE=72000000
RCC.SYSCLKSource=RCC_SYSCLKSOURCE_PLLCLK
board=custom

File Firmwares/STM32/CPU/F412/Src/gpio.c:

/* USER CODE BEGIN Header */
/**
  ******************************************************************************
  * @file    gpio.c
  * @brief   This file provides code for the configuration
  *          of all used GPIO pins.
  ******************************************************************************
  * @attention
  *
  * Copyright (c) 2023 STMicroelectronics.
  * All rights reserved.
  *
  * This software is licensed under terms that can be found in the LICENSE file
  * in the root directory of this software component.
  * If no LICENSE file comes with this software, it is provided AS-IS.
  *
  ******************************************************************************
  */
/* USER CODE END Header */

/* Includes ------------------------------------------------------------------*/
#include "gpio.h"

/* USER CODE BEGIN 0 */

/* USER CODE END 0 */

/*----------------------------------------------------------------------------*/
/* Configure GPIO                                                             */
/*----------------------------------------------------------------------------*/
/* USER CODE BEGIN 1 */

/* USER CODE END 1 */

/** Configure pins as
        * Analog
        * Input
        * Output
        * EVENT_OUT
        * EXTI
        * Free pins are configured automatically as Analog (this feature is enabled through
        * the Code Generation settings)
*/
void MX_GPIO_Init(void)
{

  GPIO_InitTypeDef GPIO_InitStruct = {0};

  /* GPIO Ports Clock Enable */
  __HAL_RCC_GPIOC_CLK_ENABLE();
  __HAL_RCC_GPIOH_CLK_ENABLE();
  __HAL_RCC_GPIOA_CLK_ENABLE();
  __HAL_RCC_GPIOB_CLK_ENABLE();
  __HAL_RCC_GPIOD_CLK_ENABLE();

  /*Configure GPIO pin Output Level */
  HAL_GPIO_WritePin(RS485_DIR_GPIO_Port, RS485_DIR_Pin, GPIO_PIN_RESET);

  /*Configure GPIO pin Output Level */
  HAL_GPIO_WritePin(GPIOB, LED_ERROR_Pin|LED_RUN_Pin|LED_FLASH_Pin|LED_HEARTBEAT_Pin
                          |LED_BOOT_Pin, GPIO_PIN_RESET);

  /*Configure GPIO pins : PC13 PC0 PC1 PC2
                           PC3 PC4 PC5 PC6
                           PC7 PC12 */
  GPIO_InitStruct.Pin = GPIO_PIN_13|GPIO_PIN_0|GPIO_PIN_1|GPIO_PIN_2
                          |GPIO_PIN_3|GPIO_PIN_4|GPIO_PIN_5|GPIO_PIN_6
                          |GPIO_PIN_7|GPIO_PIN_12;
  GPIO_InitStruct.Mode = GPIO_MODE_ANALOG;
  GPIO_InitStruct.Pull = GPIO_NOPULL;
  HAL_GPIO_Init(GPIOC, &GPIO_InitStruct);

  /*Configure GPIO pins : PA0 PA1 PA4 PA5
                           PA7 PA15 */
  GPIO_InitStruct.Pin = GPIO_PIN_0|GPIO_PIN_1|GPIO_PIN_4|GPIO_PIN_5
                          |GPIO_PIN_7|GPIO_PIN_15;
  GPIO_InitStruct.Mode = GPIO_MODE_ANALOG;
  GPIO_InitStruct.Pull = GPIO_NOPULL;
  HAL_GPIO_Init(GPIOA, &GPIO_InitStruct);

  /*Configure GPIO pins : PB0 PB1 PB2 PB10
                           PB12 PB13 PB14 */
  GPIO_InitStruct.Pin = GPIO_PIN_0|GPIO_PIN_1|GPIO_PIN_2|GPIO_PIN_10
                          |GPIO_PIN_12|GPIO_PIN_13|GPIO_PIN_14;
  GPIO_InitStruct.Mode = GPIO_MODE_ANALOG;
  GPIO_InitStruct.Pull = GPIO_NOPULL;
  HAL_GPIO_Init(GPIOB, &GPIO_InitStruct);

  /*Configure GPIO pin : PtPin */
  GPIO_InitStruct.Pin = RS485_DIR_Pin;
  GPIO_InitStruct.Mode = GPIO_MODE_OUTPUT_PP;
  GPIO_InitStruct.Pull = GPIO_NOPULL;
  GPIO_InitStruct.Speed = GPIO_SPEED_FREQ_LOW;
  HAL_GPIO_Init(RS485_DIR_GPIO_Port, &GPIO_InitStruct);

  /*Configure GPIO pin : PD2 */
  GPIO_InitStruct.Pin = GPIO_PIN_2;
  GPIO_InitStruct.Mode = GPIO_MODE_ANALOG;
  GPIO_InitStruct.Pull = GPIO_NOPULL;
  HAL_GPIO_Init(GPIOD, &GPIO_InitStruct);

  /*Configure GPIO pins : PBPin PBPin PBPin PBPin
                           PBPin */
  GPIO_InitStruct.Pin = LED_ERROR_Pin|LED_RUN_Pin|LED_FLASH_Pin|LED_HEARTBEAT_Pin
                          |LED_BOOT_Pin;
  GPIO_InitStruct.Mode = GPIO_MODE_OUTPUT_PP;
  GPIO_InitStruct.Pull = GPIO_NOPULL;
  GPIO_InitStruct.Speed = GPIO_SPEED_FREQ_LOW;
  HAL_GPIO_Init(GPIOB, &GPIO_InitStruct);

}

/* USER CODE BEGIN 2 */

/* USER CODE END 2 */

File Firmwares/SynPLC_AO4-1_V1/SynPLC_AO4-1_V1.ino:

#include "Arduino.h"
#include <SPI.h>

#define D0 A0
#define D1 A1
#define D2 A2
#define D3 A3
#define D4 A4
#define D5 A5
#define D6 A6
#define D7 A7
#define DIR 2
#define LEDs 3
#define OUTs 4
#define IN_Clk 5
#define IN_EN 6
#define ADR 7

//DAC-Control
#define NOP 0x00
#define write_dac_data 0x01
#define read_dac_register 0x02
#define write_control_register 0x55
#define write_reset_register 0x56
#define write_config_register 0x57
#define write_gain_calibration 0x58
#define write_zero_calibration 0x59
#define reset_watchdog_timer 0x95

byte adress = 0;

void setup()
{
    Serial.begin(250000);
    //SPI.beginTransaction(SPISettings(10000000, MSBFIRST, SPI_MODE0));
    pinMode(D0, INPUT);
    pinMode(D1, INPUT);
    pinMode(D2, INPUT);
    pinMode(D3, INPUT);
    pinMode(D4, INPUT);
    pinMode(D5, INPUT);
    pinMode(D6, INPUT);
    pinMode(D7, INPUT);
    pinMode(DIR, OUTPUT);
    pinMode(ADR, OUTPUT);
    pinMode(IN_Clk, OUTPUT);
    pinMode(IN_EN, OUTPUT);

    digitalWrite(ADR, HIGH);
    digitalWrite(LEDs, LOW);
    digitalWrite(OUTs, LOW);
    digitalWrite(DIR, LOW);
    digitalWrite(IN_Clk, LOW);
    digitalWrite(IN_EN, HIGH);


    get_adress();
    SPI.begin();
}

void loop()
{

}

void get_adress()
{
    bool adr0, adr1, adr2, adr3, adr4, adr5, adr6, adr7;

    digitalWrite(ADR, LOW);
    adr0 = !digitalRead(D0);
    adr1 = !digitalRead(D1);
    adr2 = !digitalRead(D2);
    adr3 = !digitalRead(D3);
    adr4 = 0;
    adr5 = 0;
    adr6 = 1;
    adr7 = 0;
    digitalWrite(ADR, HIGH);

    adress = D0 + 2*D1 + 4*D2 + 8*D3 + 16*D4 + 32*D5 + 64*D6 + 128*D7;
}

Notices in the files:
parts and their libraries:
SparkFun-Connectors: Licensing: Creative Commons ShareAlike 4.0 International - https://creativecommons.org/licenses/by-sa/4.0
crystal-geyer_V1_0: Copyright: Geyer-Electronic
